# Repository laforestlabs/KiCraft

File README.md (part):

# KiCraft

KiCad PCB automation toolkit — automated placement, routing, scoring, and
experiment management for KiCad projects via the pcbnew Python API.

## Layers

KiCraft is a multi-layer pipeline. Top-down:

1. **KiCraft** (portable Agent Skills + Python helpers) -- turns a natural-
   language project description into the hierarchical KiCad 9 file set
   (root + leaf `.kicad_sch`, `.kicad_pro`, `_autoplacer.json`). The five
   LLM-authored stages live in standards-compliant skills under
   `.agents/skills/`; deterministic validation, synthesis, placement, routing,
   and fab export are Python CLIs. See [KiCraft](#kicraft-chat--kicad-files).
2. **placement + routing + scoring** (Python, this repo) -- everything below.

## Web clarification policy

The board composer places **Auto default questions?** below the brief, checked
by default. Uncheck it to answer design ambiguities yourself. The choice belongs
to the project: reopening, answering, recovery re-drives, and cloning retain it;
**New design** resets it to checked.

Interactive questions offer ordered choices with the first labeled
**Recommended default**, plus a freeform answer field. Recommendations are not
preselected: every blocking question needs an answer before continuing. Older
saved questions without recorded choices remain answerable as freeform text.
Automatic handling does not waive electrical gates or invent missing physical
requirements; unresolved internal BOM repair fails rather than asking the user
to choose a fabricated recommendation.

Stage tabs reflect streamed native/current stage events while the run is active:
amber for active or parked, green for complete, red for failure, and yellow for
warning. Icons and accessible status names distinguish states independently of
color, including on mobile.

### What the page claims: assurance and export labels

Every project carries one derived **assurance** reading, shown next to its status
and above any download. It is derived from that project's own persisted evidence
(committed stages, stage outcomes and diagnostics, review findings, the build
gate and synthesis-check summaries, and any independent verification recorded for
the run) — it is not a separate status database, so reopening a project derives
the same answer.
Completion headlines and badges describe generation, not independent product
acceptance; the assurance reading separately exposes recorded gaps and verification.

- **Software-verified complete export** — a *current*, artifact-hash-bound
  independent verification (an acceptance audit or filled acceptance evidence)
  matches this exact export. Hardware qualification is still the user's to get.
- **Generated package · independently unverified** — a clean,
  fabrication-gate-passing export with nothing recorded to review. Downloadable,
  but *not* independently verified as fulfilling the original brief. Parts
  coverage, a committed review stage, or the presence of a downloadable package
  never make an export "verified".
- **Generated with recorded gaps · review required** — the same export plus
  recorded limitations (compiler advisories, model-declared pin claims for
  unreviewed parts, unresolved requirements, review blockers, fabrication
  cautions, unapproved changes to a required part).
- **Recorded capability limitation** — an explicit reviewed-library or recipe
  resource diagnostic stopped a requirement. A compiler contract, malformed
  candidate or procurement rejection alone is an **Incomplete or failed preview**,
  not evidence that the user's requirement is unsupported. A failed search is
  not proof the circuit is impossible.
- **Incomplete or failed preview** / **Stale preview** — the build failed or
  exhausted its recovery, or the board on disk belongs to an earlier accepted
  design (an upstream edit invalidated it). The artifacts stay viewable as
  history; the page does not offer them as this design's export.
- **Waiting for your answer** — the run is parked on an unanswered blocking
  question.

Part changes are reported honestly. A substitution the BOM ledger records for a
part the **user required** is a change, not consent: unless a recorded answer
from the user approves it, the export is labelled review-required and the change
is listed as having no recorded approval. An automatic default recorded on a
cosmetic question, and a model-selected part's automatic alternative, are listed
as actions KiCraft took — never as the user's approval.

STEP exports additionally report their actual assembly-reference coverage.
Missing component bodies and unknown coverage are explicit; a model occurrence
does not qualify geometry, clearance or the rendered image. See
[`docs/ARTIFACTS.md`](docs/ARTIFACTS.md) for the package receipt and coverage contract.

### Account admission and billing safety

Design creation reserves verification, rolling tier quota and visibility in one
SQLite transaction; a separate quota pre-check does not authorize an insert.
Invite redemption and single-use account tokens are likewise atomic. Login
attempts are limited per account and trusted ASGI peer, not caller-supplied
forwarding headers.

Stripe customer and Checkout creation use durable idempotency keys and
single-owner admission. Pre-cutover open sessions/subscriptions are reconciled
before creating another chargeable session; mismatched or uncertain state is
refused. Account deletion settles open Checkout and confirms subscription
cancellation before removing local billing linkage. Unresolved requests older
than the safe idempotency window require reconciliation, not a new key.

Build jobs and project updates carry attempt generations. A prior failed worker
cannot finalize or reap a newer attempt. Cloning preserves only the selected
generation and rebases its own artifact paths; a saved design without generated
artifacts can still be cloned, without advertising an old package.

## Installation

```bash
# Development install (editable). Synthesis imports KiCad 9's bundled
# `pcbnew`; system Python already has it. For an isolated venv, create it
# with `--system-site-packages` so `pcbnew` is visible (see pipx note below).
pip install -e .

# With KiCraft design helpers (Pydantic, kicad-skip, and easyeda2kicad).
# The ordinary skill uses the active agent's configured LLM; KiCraft itself
# needs provider credentials only for the provider-backed debug/server path.
pip install -e ".[design]"

# With all optional dependencies
pip install -e ".[scoring,experiment,design,tuning,server,loadtest,dev]"
```

### End-user install (pipx)

`kicraft build` imports KiCad's bundled `pcbnew`, and
`add-part --from-lcsc` imports `easyeda2kicad`. An isolated pipx venv sees
neither by default, so install with `--system-site-packages` and the
`[design]` extra:

```bash
pipx install --system-site-packages "kicraft[design]"
```

Already installed without them? Symptoms are `add-part --from-lcsc` printing
`easyeda2kicad not installed`, or `synthesize` raising
`ModuleNotFoundError: pcbnew`. Remediate with:

```bash
pipx reinstall --system-site-packages kicraft
pipx inject kicraft easyeda2kicad   # only if the [design] extra was omitted
```

## KiCraft (chat -> KiCad files)

A multi-turn agent workflow that takes a project description in plain English
and emits the hierarchical KiCad 9 file set consumed by placement and routing.
No prior schematic is required.

### Architecture

- The five design stages (`intent`, `functional_spec`, `architecture`, `bom`,
  and `wiring`) use the `ConversationState` Pydantic schema in
  `.kicraft/state.json`.
  Completion uses the shared `stage_done` rule, not merely nonempty connections:
  a BOM can already contain compiler-owned support wiring. A successful BOM commit
  sets `wiring_complete: false`; successful wiring acceptance sets it to `true`.
  Legacy states without the marker retain status/ownership-aware recovery.
- Portable Agent Skills live under `.agents/skills/`. The ordinary `kicraft`
  skill uses whichever LLM the active agent runtime provides.
- `.omp/config.yml` points OMP at that generic directory as a custom skill
  source, so the repository skills override stale user-level copies with the
  same names.
- The optional `kicraft-debug` skill calls the production provider-backed stage
  runtime. It runs in two modes: interactive, which pauses before each durable commit for
  explicit review, and loop, which drives every stage to a committed board unattended,
  defaults anything the design can absorb (recording and analysing each default), and stops
  only on a failure it cannot repair. Both modes keep the same audit trail under
  `.kicraft/debug/`.
- The deterministic synthesis/build step is the `kicraft` CLI.

### Run it

Open this repository in any Agent Skills-compatible coding agent and ask it to
use the `kicraft` skill:

```text
Use the kicraft skill to design a USB-C powered 3.3 V status LED board.
```

For production-provider stage inspection:

```text
Use the kicraft-debug skill to walk through each KiCraft LLM stage.
```

Describe your project ("USB-C powered 3.3V regulator with status LED,
JLCPCB target, under $5 BOM"). The ordinary flow steps through all five
stages and commits each slot. The debug flow uses the production provider
and retains its prompt, raw response, tool trace, candidate, and diagnostics
under `.kicraft/debug/`. Interactive runs keep `.kicraft/state.json` unchanged
until explicit acceptance; loop runs commit each stage as soon as its own checks
pass, and write an end-of-run summary plus a machine-readable last line so a
wrapper can iterate. After wiring is committed, ask the ordinary skill to
run the deterministic build.

```bash
kicraft build .kicraft/state.json ./generated --quality good
```

### Using the skills in another project

Copy the standards-compliant skill directories into the target project's
`.agents/skills/` discovery root:

```bash
mkdir -p your-project/.agents/skills
cp -r /path/to/KiCraft/.agents/skills/kicraft your-project/.agents/skills/
cp -r /path/to/KiCraft/.agents/skills/kicraft-debug your-project/.agents/skills/
```

OMP users should also copy the small discovery bridge:

```bash
mkdir -p your-project/.omp
cp /path/to/KiCraft/.omp/config.yml your-project/.omp/
```

Clients that use a different Agent Skills discovery root can copy the same
skill directories there unchanged; each skill is self-contained around its
`SKILL.md`.

Install the ordinary design CLI with
`pip install -e "/path/to/KiCraft[design]"`. It uses the active agent's LLM
configuration and does not require a KiCraft provider key. The provider-backed
`kicraft-debug` skill additionally requires
`pip install -e "/path/to/KiCraft[server,design]"` and the OpenRouter
configuration used by the production web stage driver.

### Agent capabilities

The skills use generic capabilities rather than vendor-specific permission
syntax. Grant the active agent only the capabilities listed in each
`SKILL.md`: read project/skill files, write `/tmp/kicraft_*`, and run the named
`kicraft` commands. No slash commands, vendor-specific delegation API, or
vendor-specific settings file is required.

### CLI reference

```bash
kicraft stage-prep <stage> [STATE]
# Single-shot collector. Returns JSON: {state, extras} where extras carries
# the leaf-library output for architecture and BATCHED symbol pinouts for
# wiring (replacing N per-part lookup-symbol calls with one).

kicraft stage-commit <stage> --slot-file F.json \
  [--questions-file Q.json] [--history-message M] [--project-stem S] \
  [--invalidate-downstream] [STATE] [--no-archive] [--archive-root DIR]
# Atomic: validate the proposed slot, merge into state.json, append history,
# archive. Returns {"ok": true, ...} or {"ok": false, "errors": [...]} so the
# active agent can correct a rejected candidate.

kicraft-stage-debug debug-draft --workspace PATH --stage STAGE \
  --brief-file BRIEF [--instruction-file GUIDANCE] [--answers-file ANSWERS]
# Runs the production provider and atomically saves a pending review artifact
# without committing or stamping state.json.

kicraft-stage-debug debug-commit --workspace PATH --stage STAGE \
  --history-message-file MESSAGE
# Stale-hash checks state.json, commits the exact accepted slot through
# stage-commit, invalidates downstream stages, and finalizes the debug trace.

kicraft validate .kicraft/state.json
# prints {ok, project_stem, slots_filled, open_questions, blocking_questions}
# exit codes: 0 ok, 2 schema error, 3 library validation error

kicraft list-leaves
# prints the "Available leaves" markdown block. The architecture stage
# receives this via stage-prep's extras; this command is for ad-hoc inspection.

kicraft lookup-symbol Library:Name
# prints one symbol's pin inventory. The wiring stage receives all needed
# pinouts via stage-prep's batched extras; this command is for ad-hoc lookup.

kicraft synthesize .kicraft/state.json ./generated [--smoke]
# wraps kicraft.design.synthesize.run; --smoke adds the (slow)
# solve-subcircuits check
```

### What gets written

For project stem `MYPROJ`, synthesis writes:

```
MYPROJ/
  MYPROJ.kicad_sch                    # hierarchical root
  <SHEET>.kicad_sch ...               # one per leaf sheet
  MYPROJ.kicad_pro                    # design rules + Default/Power netclasses
  MYPROJ_autoplacer.json              # ic_groups, power_nets, signal_flow_order, ...
  MYPROJ.kicad_pcb                    # empty pcbnew stub
```

Managed web builds isolate each attempt under
`generated/attempt-<generation>/<STEM>/`; requeued work retains that attempt's
directory. `state.artifacts.project_dir` identifies the recorded output, but
previews and downloads must also belong to the current attempt. Older outputs
remain evidence, not current delivery.

Synthesis records hashes of the generated files it owns. An explicit CLI output
directory containing untracked or user-modified outputs is refused rather than
silently adopted or overwritten. Completed partial outputs are recorded so a
failed attempt can recover without claiming unrelated files.

Everything past that is the existing layout/routing pipeline:

```bash
cd MYPROJ
autoexperiment MYPROJ.kicad_pcb --schematic MYPROJ.kicad_sch --rounds 20
```

### Validation

Every synthesis run executes SS9.1-SS9.6 from
`docs/kicraft_schematic_prompt.md` against the written files
(schematic version, footprints non-empty, pin directions valid,
Sheetfile refs resolve, autoplacer JSON valid, every named ref in
the schematic). Synthesis raises `SynthesisValidationError` and prints
the failing check rather than shipping a broken file set.

### Notes

- Resolved curated bundles can provide project-local symbols, footprints and
  models. An unresolved or unqualified part remains blocking; a matching name
  or stock count alone does not establish electrical or physical suitability.
- State persists as `.kicraft/state.json` in the project directory —
  gitignore it (or commit it; it's plain JSON and reviewable).

## Leaf Library (reuse vetted designs across projects)

A *leaf* is a single hierarchical sheet — a pre-routed PCB fragment plus
its schematic, BOM, and autoplacer settings. Once you've solved one
("USB-C 1S LiPo charger") and pinned a round you trust, you can promote
it into the global Leaf Library. The KiCraft pipeline then reuses
it verbatim every time the LLM judges it a match for a new project,
collapsing leaf-level design surface to a vetted, pinned solution.

### Where leaves live

```
$KICRAFT_LEAF_LIB                # default: ~/.kicraft/leaves/
  usb-c-lipo-charger/
    manifest.json
    leaf_routed.kicad_pcb        # canonical name (matches .experiments/...)
    metadata.json
    solved_layout.json
    schematic.kicad_sch
    autoplacer_fragment.json
    bom.csv
    renders/
      front_all.png
      back_copper.png
      copper_both.png
      thumbnail.png
```

The pinned-PCB triad (`leaf_routed.kicad_pcb` + `metadata.json` +
`solved_layout.json`) is the same triad the existing pin manager (under
`.experiments/subcircuits/<leaf_key>/`) consumes, so an imported leaf
drops in as a pre-solved round and the parent composer treats it as
already-solved on the next `autoexperiment --parents-only`.

### Promote a leaf

> **Note:** the Experiment Manager GUI that hosted the "Leaf Library" promote flow was
> removed 2026-06-22 (recover from git history if needed). Leaf promotion is pending a
> re-home in the web app — see `docs/plans/refactor-roadmap.md`. The pinned-round import
> format described above still applies.

The wizard runs the renders, writes a manifest with the
content-addressed hash, and atomically writes the new directory into
`$KICRAFT_LEAF_LIB`. To replace an existing leaf, bump the version
(e.g. `0.1.0 -> 0.1.1` for a patch, `0.2.0` for additive interface
changes, `1.0.0` for breaking ones).

### Automatic reuse during KiCraft

When the skill enters the architecture stage it runs
`kicraft list-leaves` and reads the result so the model can
see the curated catalog. The active agent picks matches by setting
`Sheet.from_library = "<name>@<version>"` and `Sheet.library_instance = N`.
`kicraft validate` then verifies the leaf's hierarchical-
label interface matches the sheet's endpoints exactly. Synthesis then:

1. Skips the LLM-generated leaf schematic for that sheet.
2. Copies the leaf's `schematic.kicad_sch` to the project (with refdes
   renumbered to fit the host project's existing refs).
3. Writes the renumbered triad into
   `<project>/.experiments/subcircuits/<leaf_key>/round_lib0001_*`.
4. Pins the import via `pins.json` so `ensure_applied()` keeps it locked
   across solver runs.
5. Adds a `library_leaves` audit record to `<project>_autoplacer.json`.

### CLI

```bash
kicraft-leaf list             # rows: name@version, hash, tags, description
kicraft-leaf show <name>      # full manifest as JSON
kicraft-leaf path             # resolved library directory
```

Promotion and removal are GUI-only — there's no `kicraft-leaf promote`.
The intent is that curating the library is a deliberate, human-in-loop
step, not a scriptable one.

## Quick Start

KiCraft is project-agnostic. Create a `<project>_autoplacer.json` (or
`autoplacer.json`) in your KiCad project root to configure IC groups,
component zones, signal flow, and other project-specific settings.

See `examples/llups_autoplacer.json` for a full example.

### Solve subcircuits

```bash
cd /path/to/your/kicad-project
solve-subcircuits project.kicad_sch --pcb project.kicad_pcb --rounds 3 --route
```

### Run experiment loop

```bash
autoexperiment project.kicad_pcb project.kicad_sch --rounds 20 --workers 2
```

### Two-phase guided experiment (leaf pinning)

Explore leaf candidates first, lock the ones you like, then iterate on the
parent only:

```bash
# 1. Solve only leaves -- snapshots every round to .experiments/subcircuits/<leaf>/round_NNNN_*
autoexperiment project.kicad_pcb --schematic project.kicad_sch --rounds 30 --leaves-only

# 2. Pin chosen rounds via the GUI Analysis page (Hierarchical Progression -> Accepted
#    Leaf Gallery -> "Pin from prior experiment-round snapshots"), or write
#    .experiments/pins.json by hand.

# 3. Run only the parent compose phase against the pinned leaves
autoexperiment project.kicad_pcb --schematic project.kicad_sch --rounds 10 --parents-only
```

The composer calls `pins.ensure_applied()` before loading artifacts, so
pinned leaves stay locked even if a stray leaf-solve overwrites the
canonical files. The best parent of any run is also copied to
`.experiments/best/parent_routed.kicad_pcb` and `<projectname>_best.kicad_pcb`
at the project root for fab handoff.

### Score a layout

```bash
score-layout project.kicad_pcb
```

### Configuring Placement

Placement constraints live in `<project>_autoplacer.json` at the project
root. The autoplacer auto-discovers it; the file is project-agnostic --
it references components by ref designator (e.g. `J1`) or subcircuit
sheet name (e.g. `BATT`), nothing is hardcoded to a particular project.
See `examples/llups_autoplacer.json` for a full working file.

#### Pinning components to edges, corners, or zones

`component_zones` constrains where individual refs land on the board.
Three constraint types, all applied at solve time:

```json
{
  "component_zones": {
    "J1":  { "edge":   "left" },
    "J2":  { "edge":   "right" },
    "H4":  { "corner": "top-left" },
    "H86": { "corner": "bottom-right" },
    "BT1": { "zone":   "bottom" },
    "BT2": { "zone":   "bottom" }
  }
}
```

* `edge: left|right|top|bottom` — connector body flush with the named
  edge. Pads face inward, housing overhangs outward by
  `connector_edge_inset_mm`.
* `corner: top-left|top-right|bottom-left|bottom-right` — typically
  mounting holes. Locks at the corner with `mounting_holes.keepout.size_mm`
  reserved (see [Mounting holes](#mounting-holes) below).
* `zone: top|bottom|left|right|...` — soft confinement to a region.
  The component is locked inside the zone; the solver may place it
  anywhere within it.

When a ref is part of a child subcircuit (e.g. `BT1` inside the `BATT`
subcircuit), the constraint is propagated to the *block* during parent
composition, so the BATT block ends up zone-bottom-pinned at parent
solve time.

#### Backside THT components: enabling stacking

By default, the parent composer prevents two leaves from overlapping
when both have any same-layer copper -- a strict same-layer-outline
gate that catches CHARGER-style continuous-F.Cu shorts. PTH pads
register as copper on **both** F.Cu and B.Cu, so a leaf whose only
front-side copper is the shadow of through-hole pads (battery
holders, screw terminals, large barrel jacks) is treated as having
real F.Cu occupancy and rejects SMT-on-front stacking inside its
bbox -- even when the body centre is empty and stacking would be
physically fine.

To re-enable opposite-side stacking on top of such a leaf, open the
GUI's **Setup → Per-Component Placement Rules** tab, expand the leaf,
and toggle the sheet-level switch:

> ☐ → ☑ **Backside THT anchor (allow SMT-front leaves to stack on top)**

Click **Save to project JSON…**, review the diff modal, and confirm.
The toggle persists as a sheet-name entry under
`parent_placement.backside_through_hole_leaves`. For headless or CI
workflows the same key can be set by hand:

```json
{
  "parent_placement": {
    "backside_through_hole_leaves": ["BATT", "TERMINAL_BLOCK"]
  }
}
```

What the override does:

* Marks the leaf as having no F.Cu intent for the same-layer-outline
  gate, so SMT-on-front leaves may overlap inside its bbox.
* Tells the post-SA stack pass (`_stack_compatible_blocks`) to use
  it as a stacking anchor, actively row-packing front-only candidates
  inside its body.
* Leaves the per-pad sparse-rect overlap checks in place -- if a
  candidate's pads happen to land on the THT pads themselves
  (corner positions), the predicate still rejects that specific
  geometry.

The flag is keyed by `sheet_name` so any project can list its own
THT-back leaves; nothing is hardcoded to a single board. CHARGER-style
leaves with continuous F.Cu routing **must not** be enabled -- the
override there would let the original same-layer shorts return.

#### Candidate search

`parent_placement.candidate_search` controls the K-candidate search
loop. The picker stamps each candidate, runs DRC, scores by a
composite of opposite-side packing, courtyard overlap, ratsnest
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
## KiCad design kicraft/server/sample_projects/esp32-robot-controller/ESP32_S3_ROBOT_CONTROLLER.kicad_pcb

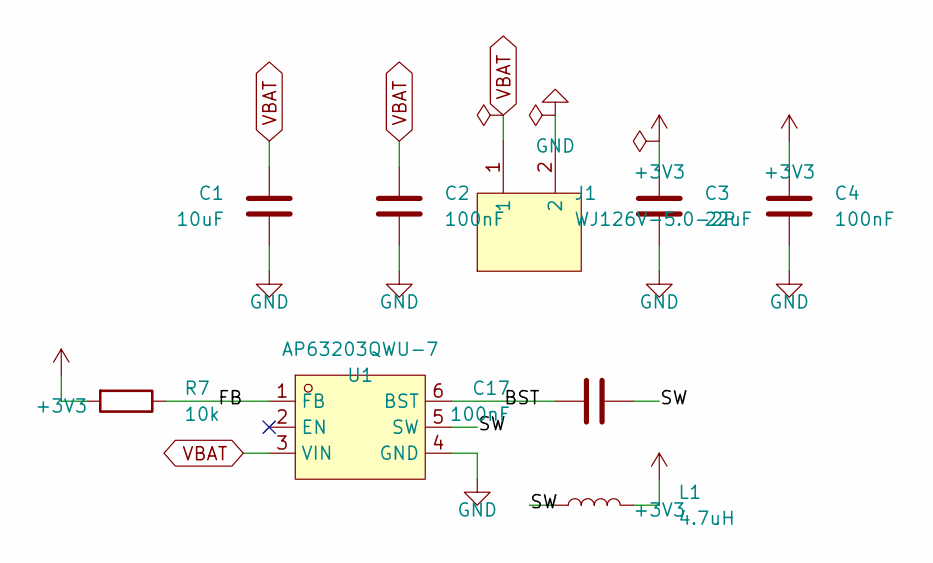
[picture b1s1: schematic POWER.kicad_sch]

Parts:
C1: 10uF; C_0805_2012Metric
C2, C4, C17: 100nF; C_0603_1608Metric
C3: 22uF; C_0805_2012Metric
J1: WJ126V-5.0-2P; CONN-TH_WJ126V-5.0-2P
L1: 4.7uH; L_0805_2012Metric
R7: 10k; R_0603_1608Metric
U1: AP63203QWU-7; TSOT-26_L2.9-W1.6-P0.95-LS2.8-BL

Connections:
BST: C17.1, U1.6 (BST)
FB: R7.1, U1.1 (FB)
SW: C17.2, L1.1, U1.5 (SW)

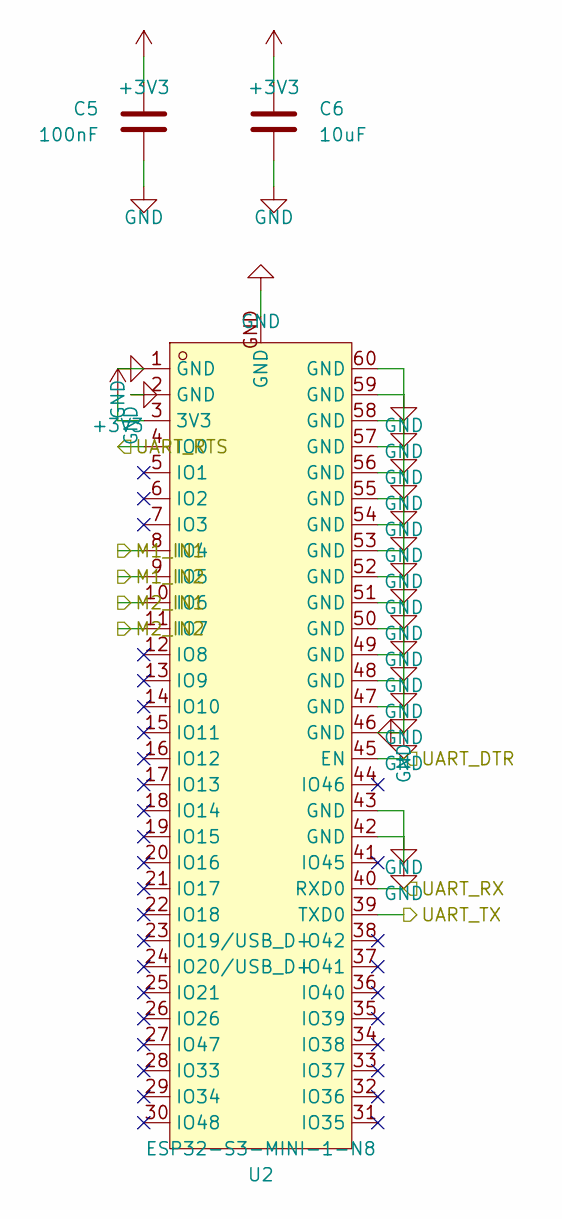
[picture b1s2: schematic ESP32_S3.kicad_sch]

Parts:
C5: 100nF; C_0603_1608Metric
C6: 10uF; C_0805_2012Metric
U2: ESP32-S3-MINI-1-N8; BULETM-SMD_ESP32-S3-MINI-1-N8

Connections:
M1_IN1: U2.8 (IO4); also elsewhere on the board
M1_IN2: U2.9 (IO5); also elsewhere on the board
M2_IN1: U2.10 (IO6); also elsewhere on the board
M2_IN2: U2.11 (IO7); also elsewhere on the board
UART_DTR: U2.45 (EN); also elsewhere on the board
UART_RTS: U2.4 (IO0); also elsewhere on the board
UART_RX: U2.40 (RXD0); also elsewhere on the board
UART_TX: U2.39 (TXD0); also elsewhere on the board

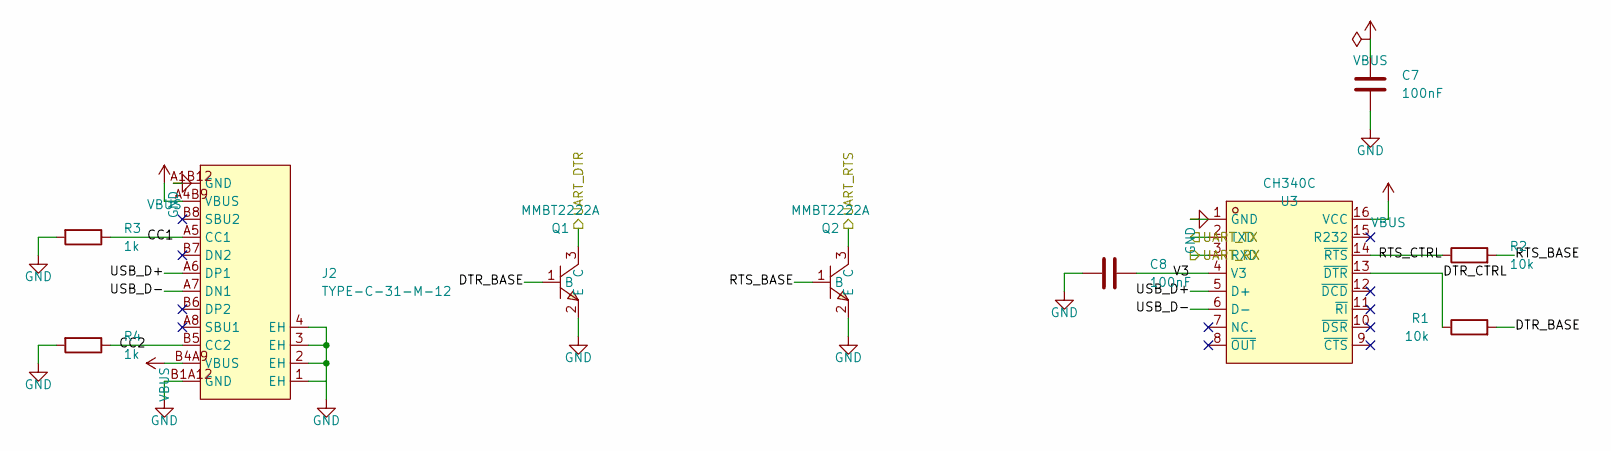
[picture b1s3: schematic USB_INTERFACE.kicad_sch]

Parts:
C7, C8: 100nF; C_0603_1608Metric
J2: TYPE-C-31-M-12; USB-C_SMD-TYPE-C-31-M-12_1
Q1, Q2: MMBT2222A; SOT-23-3_L2.9-W1.3-P1.90-LS2.4-BR
R1, R2: 10k; R_0603_1608Metric
R3, R4: 1k; R_0603_1608Metric
U3: CH340C; SOP-16_L10.0-W3.9-P1.27-LS6.0-BL

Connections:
CC1: J2.A5 (CC1), R3.1
CC2: J2.B5 (CC2), R4.1
DTR_BASE: Q1.1 (B), R1.2
DTR_CTRL: R1.1, U3.13 (~DTR)
RTS_BASE: Q2.1 (B), R2.2
RTS_CTRL: R2.1, U3.14 (~RTS)
UART_DTR: Q1.3 (C); also elsewhere on the board
UART_RTS: Q2.3 (C); also elsewhere on the board
UART_RX: U3.3 (RXD); also elsewhere on the board
UART_TX: U3.2 (TXD); also elsewhere on the board
USB_D+: J2.A6 (DP1), U3.5 (D+)
USB_D-: J2.A7 (DN1), U3.6 (D-)
V3: C8.1, U3.4 (V3)
VBUS: C7.1, J2.A4B9 (VBUS), J2.B4A9 (VBUS), U3.16 (VCC)

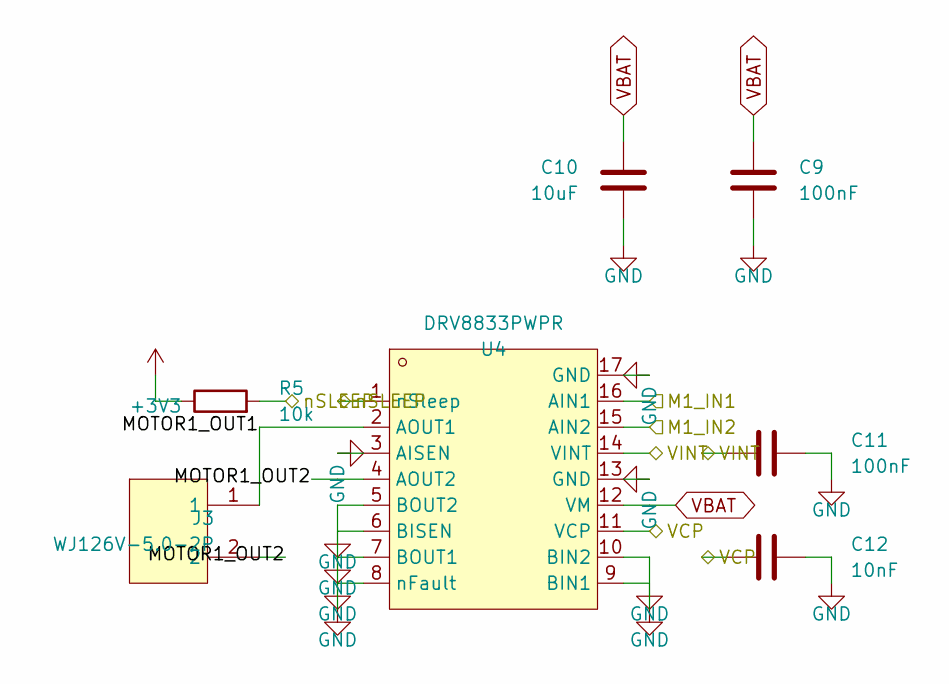
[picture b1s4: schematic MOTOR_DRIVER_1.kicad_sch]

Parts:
C9, C11: 100nF; C_0603_1608Metric
C10: 10uF; C_0805_2012Metric
C12: 10nF; C_0603_1608Metric
J3: WJ126V-5.0-2P; CONN-TH_WJ126V-5.0-2P
R5: 10k; R_0603_1608Metric
U4: DRV8833PWPR; TSSOP-16_L5.0-W4.4-P0.65-LS6.4-BL-EP

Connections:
M1_IN1: U4.16 (AIN1); also elsewhere on the board
M1_IN2: U4.15 (AIN2); also elsewhere on the board
MOTOR1_OUT1: J3.1, U4.2 (AOUT1)
MOTOR1_OUT2: J3.2, U4.4 (AOUT2)
VCP: C12.1, U4.11 (VCP); also elsewhere on the board
VINT: C11.1, U4.14 (VINT); also elsewhere on the board
nSLEEP: R5.2, U4.1 (nSleep); also elsewhere on the board

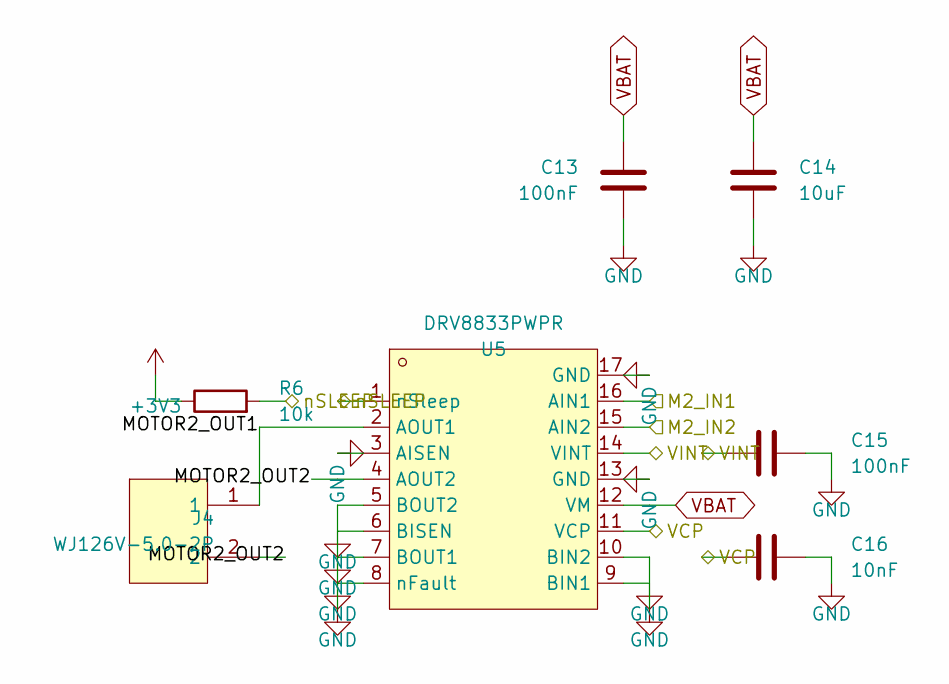
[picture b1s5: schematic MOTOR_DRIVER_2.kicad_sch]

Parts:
C13, C15: 100nF; C_0603_1608Metric
C14: 10uF; C_0805_2012Metric
C16: 10nF; C_0603_1608Metric
J4: WJ126V-5.0-2P; CONN-TH_WJ126V-5.0-2P
R6: 10k; R_0603_1608Metric
U5: DRV8833PWPR; TSSOP-16_L5.0-W4.4-P0.65-LS6.4-BL-EP

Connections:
M2_IN1: U5.16 (AIN1); also elsewhere on the board
M2_IN2: U5.15 (AIN2); also elsewhere on the board
MOTOR2_OUT1: J4.1, U5.2 (AOUT1)
MOTOR2_OUT2: J4.2, U5.4 (AOUT2)
VCP: C16.1, U5.11 (VCP); also elsewhere on the board
VINT: C15.1, U5.14 (VINT); also elsewhere on the board
nSLEEP: R6.2, U5.1 (nSleep); also elsewhere on the board

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
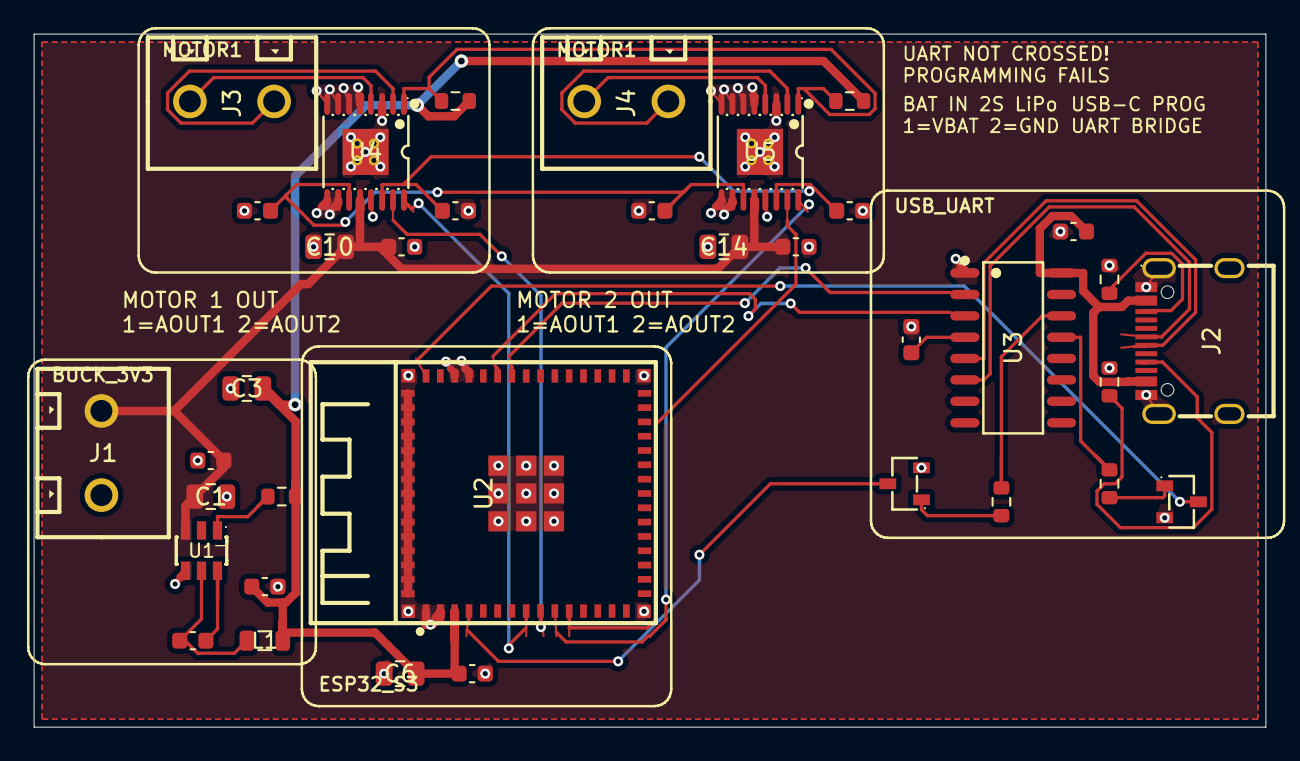
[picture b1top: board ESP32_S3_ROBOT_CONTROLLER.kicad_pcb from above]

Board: 2 copper layers, 73.2 x 41.2 mm, 36 parts (0 on the bottom side), 31 nets.

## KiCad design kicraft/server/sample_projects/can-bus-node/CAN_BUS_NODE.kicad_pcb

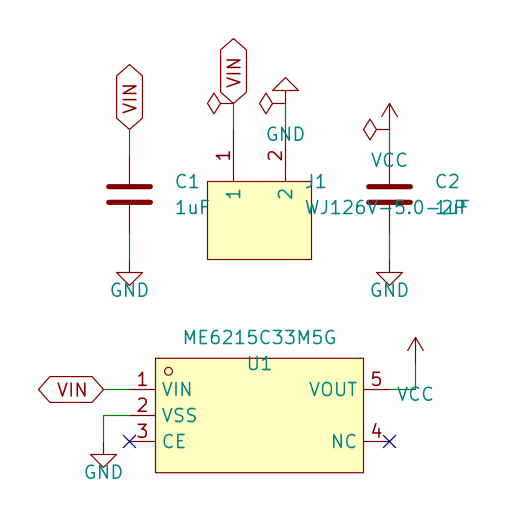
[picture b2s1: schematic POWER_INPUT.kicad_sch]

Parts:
C1, C2: 1uF; C_0603_1608Metric
J1: WJ126V-5.0-2P; CONN-TH_WJ126V-5.0-2P
U1: ME6215C33M5G; SOT-23-5_L3.0-W1.7-P0.95-LS2.8-BR

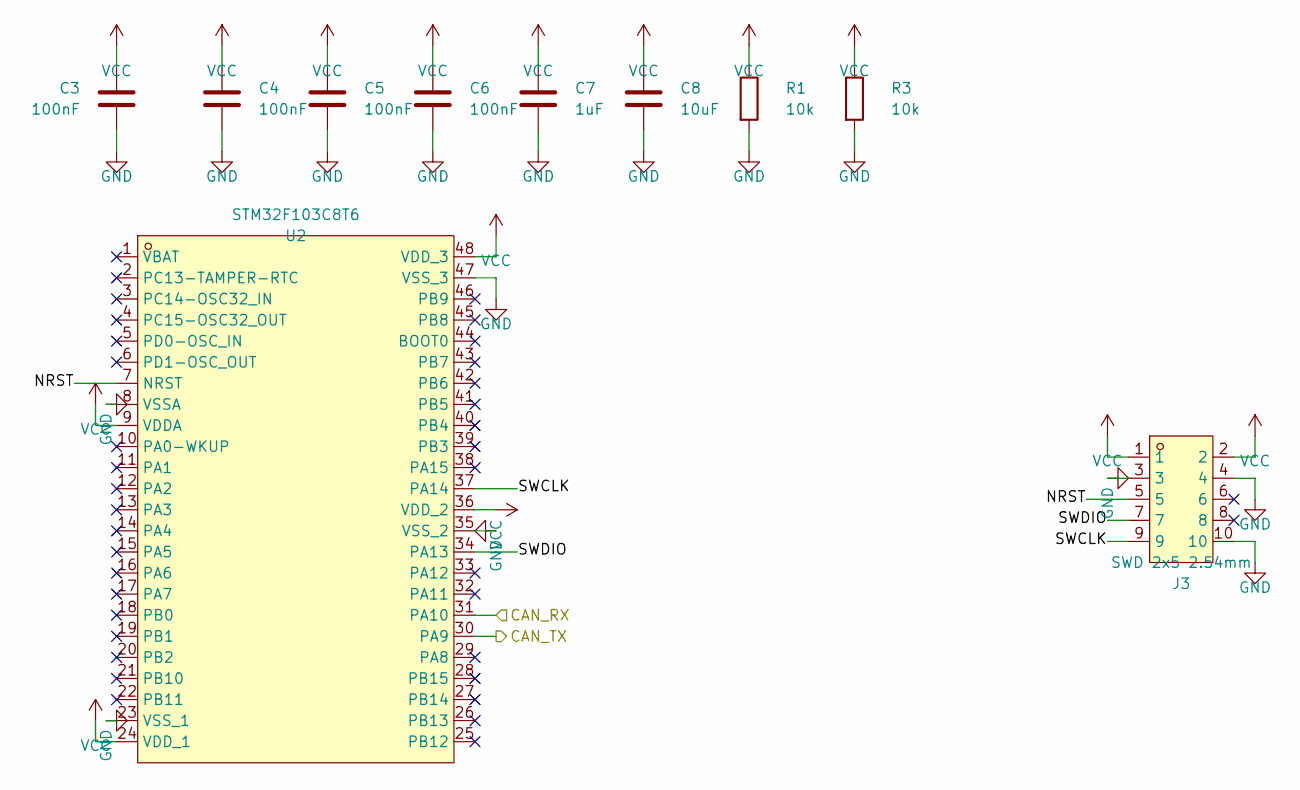
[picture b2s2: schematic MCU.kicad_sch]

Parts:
C3, C4, C5, C6: 100nF; C_0603_1608Metric
C7: 1uF; C_0603_1608Metric
C8: 10uF; C_0603_1608Metric
J3: SWD 2x5 2.54mm; HDR-TH_10P-P2.54-V-M-R2-C5-S2.54
R1, R3: 10k; R_0603_1608Metric
U2: STM32F103C8T6; LQFP-48_L7.0-W7.0-P0.50-LS9.0-BL

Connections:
CAN_RX: U2.31 (PA10); also elsewhere on the board
CAN_TX: U2.30 (PA9); also elsewhere on the board
NRST: J3.5, U2.7 (NRST)
SWCLK: J3.9, U2.37 (PA14)
SWDIO: J3.7, U2.34 (PA13)

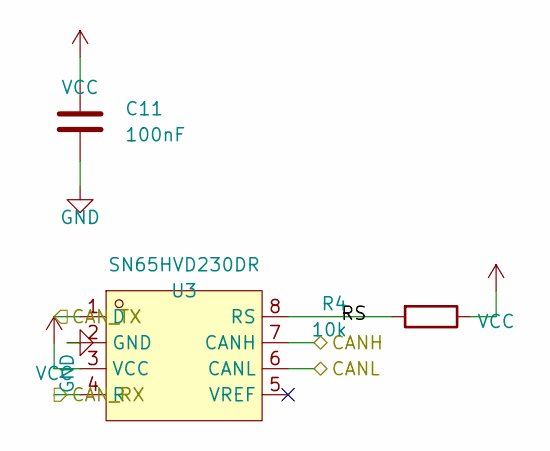
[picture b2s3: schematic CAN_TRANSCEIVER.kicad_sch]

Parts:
C11: 100nF; C_0603_1608Metric
R4: 10k; R_0603_1608Metric
U3: SN65HVD230DR; SOIC-8_L4.9-W3.9-P1.27-LS6.0-BL

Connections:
CANH: U3.7 (CANH); also elsewhere on the board
CANL: U3.6 (CANL); also elsewhere on the board
CAN_RX: U3.4 (R); also elsewhere on the board
CAN_TX: U3.1 (D); also elsewhere on the board
RS: R4.2, U3.8 (RS)

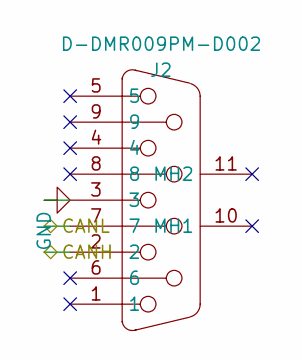
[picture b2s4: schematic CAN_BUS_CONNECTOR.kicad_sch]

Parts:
J2: D-DMR009PM-D002; DSUB-TH_DMR-9P

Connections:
CANH: J2.2; also elsewhere on the board
CANL: J2.7; also elsewhere on the board

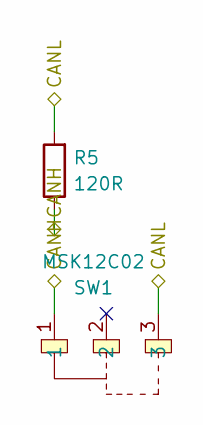
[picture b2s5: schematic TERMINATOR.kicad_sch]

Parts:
R5: 120R; R_0603_1608Metric
SW1: MSK12C02; SW-SMD_3P-L9.1-W3.5-P2.50_MST-12D18G2

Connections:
CANH: R5.1, SW1.1; also elsewhere on the board
CANL: R5.2, SW1.3; also elsewhere on the board

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
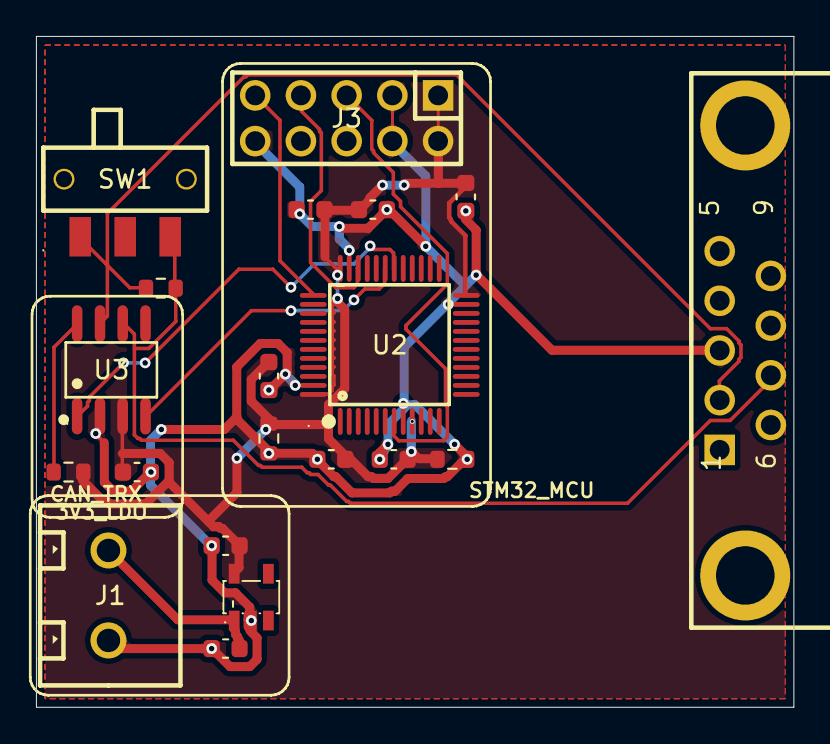
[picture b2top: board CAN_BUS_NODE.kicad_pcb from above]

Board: 2 copper layers, 42.1 x 37.3 mm, 20 parts (0 on the bottom side), 11 nets.

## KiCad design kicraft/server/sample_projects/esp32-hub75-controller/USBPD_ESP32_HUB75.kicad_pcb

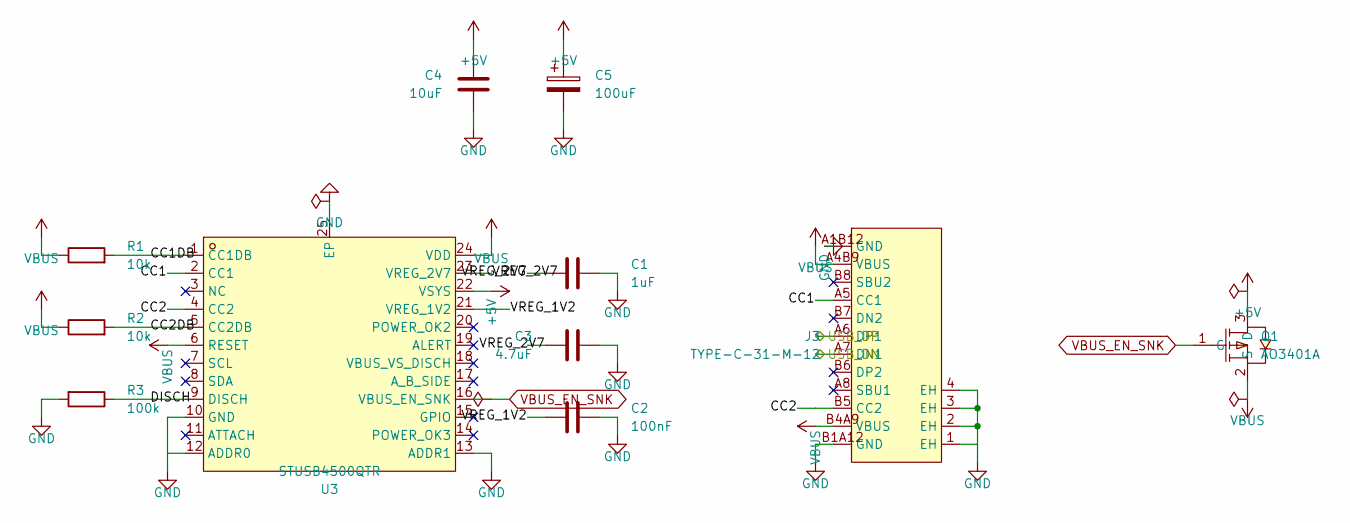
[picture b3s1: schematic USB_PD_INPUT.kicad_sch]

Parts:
C1: 1uF; C_0603_1608Metric
C2: 100nF; C_0603_1608Metric
C3: 4.7uF; C_0603_1608Metric
C4: 10uF; C_0603_1608Metric
C5: 100uF; CP_Elec_6.3x5.4
J3: TYPE-C-31-M-12; USB-C_SMD-TYPE-C-31-M-12_1
Q1: AO3401A; SOT-23_L2.9-W1.3-P1.90-LS2.4-BR
R1, R2: 10k; R_0603_1608Metric
R3: 100k; R_0603_1608Metric
U3: STUSB4500QTR; QFN-24_L4.0-W4.0-P0.50-BL-EP2.8

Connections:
CC1: J3.A5 (CC1), U3.2 (CC1)
CC1DB: R1.2, U3.1 (CC1DB)
CC2: J3.B5 (CC2), U3.4 (CC2)
CC2DB: R2.2, U3.5 (CC2DB)
DISCH: R3.1, U3.9 (DISCH)
USB_DN: J3.A7 (DN1); also elsewhere on the board
USB_DP: J3.A6 (DP1); also elsewhere on the board
VREG_1V2: C2.1, U3.21 (VREG_1V2)
VREG_2V7: C1.1, C3.1, U3.23 (VREG_2V7)

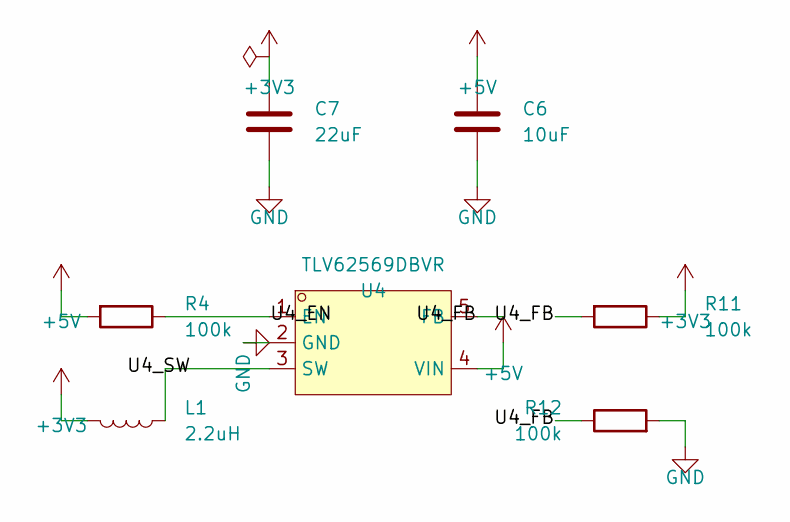
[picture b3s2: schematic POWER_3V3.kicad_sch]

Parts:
C6: 10uF; C_0603_1608Metric
C7: 22uF; C_0603_1608Metric
L1: 2.2uH; L_0805_2012Metric
R4, R11, R12: 100k; R_0603_1608Metric
U4: TLV62569DBVR; SOT-23-5_L3.0-W1.7-P0.95-LS2.8-BR

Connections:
+3V3: C7.1, L1.2, R11.1; also elsewhere on the board
U4_EN: R4.1, U4.1 (EN)
U4_FB: R11.2, R12.1, U4.5 (FB)
U4_SW: L1.1, U4.3 (SW)

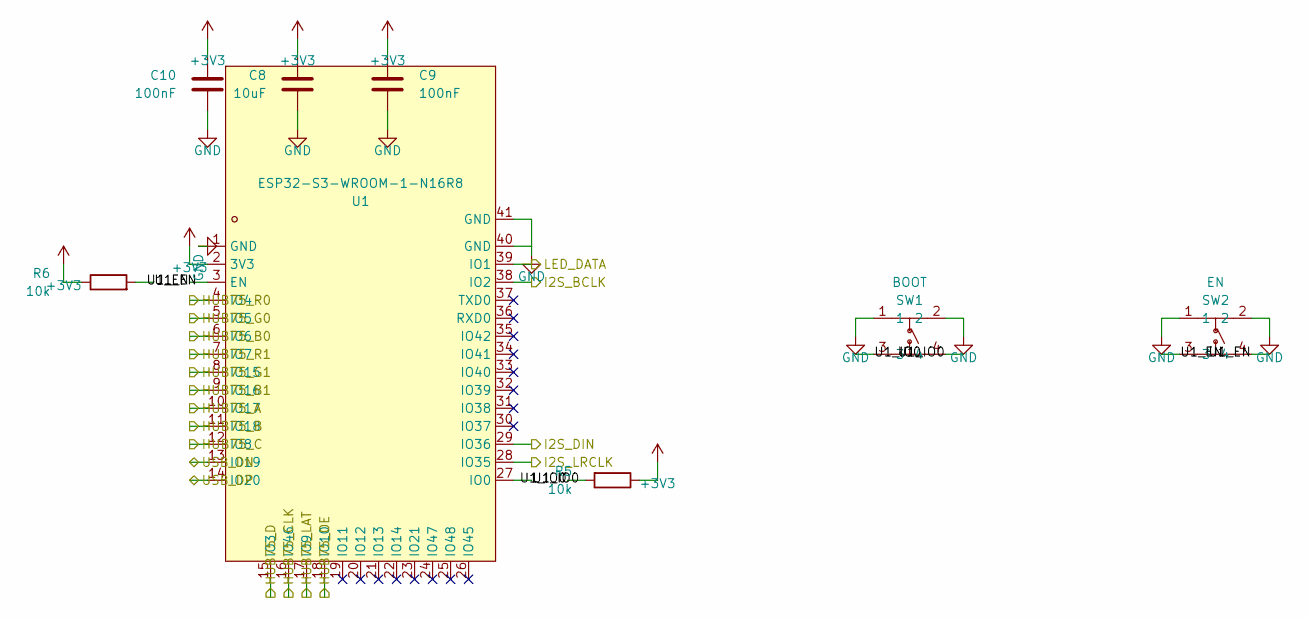
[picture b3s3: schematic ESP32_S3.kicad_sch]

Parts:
C8: 10uF; C_0603_1608Metric
C9, C10: 100nF; C_0603_1608Metric
R5, R6: 10k; R_0603_1608Metric
SW1: BOOT; SW-SMD_4P-L6.0-W6.0-P4.50-LS9.0_H5.0
SW2: EN; SW-SMD_4P-L6.0-W6.0-P4.50-LS9.0_H5.0
U1: ESP32-S3-WROOM-1-N16R8; WIRELM-SMD_ESP32-S3-WROOM-1

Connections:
+3V3: C8.1, C9.1, C10.1, R5.1, R6.1, U1.2 (3V3); also elsewhere on the board
HUB75_A: U1.10 (IO17); also elsewhere on the board
HUB75_B: U1.11 (IO18); also elsewhere on the board
HUB75_B0: U1.6 (IO6); also elsewhere on the board
HUB75_B1: U1.9 (IO16); also elsewhere on the board
HUB75_C: U1.12 (IO8); also elsewhere on the board
HUB75_CLK: U1.16 (IO46); also elsewhere on the board
HUB75_D: U1.15 (IO3); also elsewhere on the board
HUB75_G0: U1.5 (IO5); also elsewhere on the board
HUB75_G1: U1.8 (IO15); also elsewhere on the board
HUB75_LAT: U1.17 (IO9); also elsewhere on the board
HUB75_OE: U1.18 (IO10); also elsewhere on the board
HUB75_R0: U1.4 (IO4); also elsewhere on the board
HUB75_R1: U1.7 (IO7); also elsewhere on the board
I2S_BCLK: U1.38 (IO2); also elsewhere on the board
I2S_DIN: U1.29 (IO36); also elsewhere on the board
I2S_LRCLK: U1.28 (IO35); also elsewhere on the board
LED_DATA: U1.39 (IO1); also elsewhere on the board
U1_EN: R6.2, SW2.3, SW2.4, U1.3 (EN)
U1_IO0: R5.2, SW1.3, SW1.4, U1.27 (IO0)
USB_DN: U1.13 (IO19); also elsewhere on the board
USB_DP: U1.14 (IO20); also elsewhere on the board

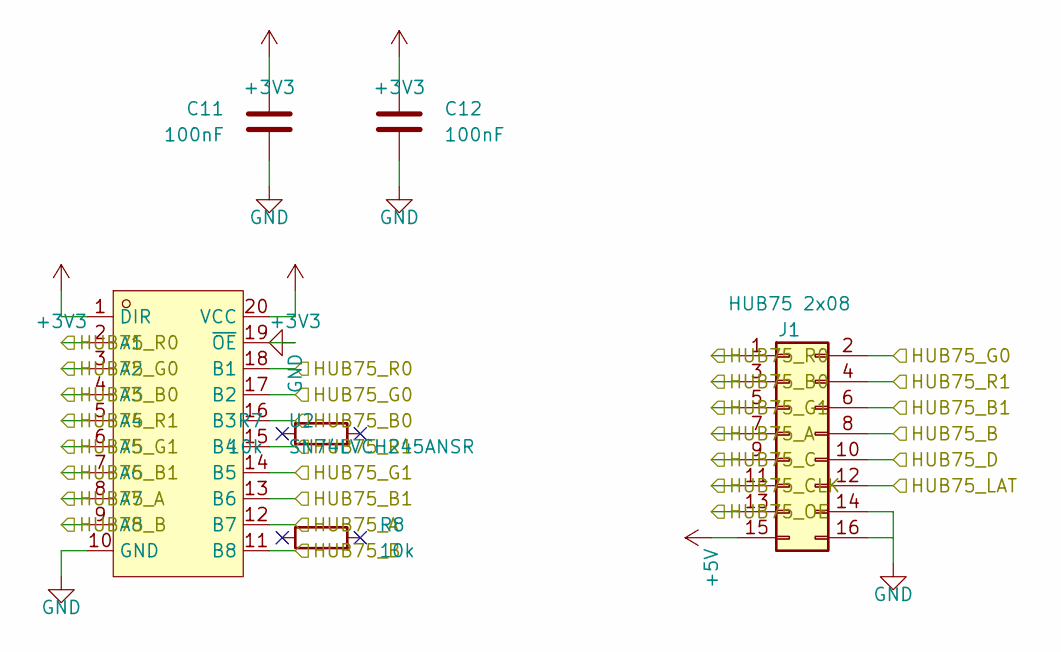
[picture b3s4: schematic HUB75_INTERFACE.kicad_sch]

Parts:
C11, C12: 100nF; C_0603_1608Metric
J1: HUB75 2x08; PinHeader_2x08_P2.54mm_Vertical
R7, R8: 10k; R_0603_1608Metric
U2: SN74LVCH245ANSR; SO-20_L12.6-W5.3-P1.27-LS7.8-BL

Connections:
+3V3: C11.1, C12.1, U2.1 (DIR), U2.20 (VCC); also elsewhere on the board
HUB75_A: J1.7, U2.8 (A7), U2.12 (B7); also elsewhere on the board
HUB75_B: J1.8, U2.9 (A8), U2.11 (B8); also elsewhere on the board
HUB75_B0: J1.3, U2.4 (A3), U2.16 (B3); also elsewhere on the board
HUB75_B1: J1.6, U2.7 (A6), U2.13 (B6); also elsewhere on the board
HUB75_C: J1.9; also elsewhere on the board
HUB75_CLK: J1.11; also elsewhere on the board
HUB75_D: J1.10; also elsewhere on the board
HUB75_G0: J1.2, U2.3 (A2), U2.17 (B2); also elsewhere on the board
HUB75_G1: J1.5, U2.6 (A5), U2.14 (B5); also elsewhere on the board
HUB75_LAT: J1.12; also elsewhere on the board
HUB75_OE: J1.13; also elsewhere on the board
HUB75_R0: J1.1, U2.2 (A1), U2.18 (B1); also elsewhere on the board
HUB75_R1: J1.4, U2.5 (A4), U2.15 (B4); also elsewhere on the board

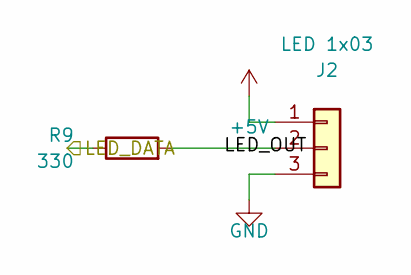
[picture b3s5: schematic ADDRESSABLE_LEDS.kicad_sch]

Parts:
J2: LED 1x03; PinHeader_1x03_P2.54mm_Vertical
R9: 330; R_0603_1608Metric

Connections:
LED_DATA: R9.1; also elsewhere on the board
LED_OUT: J2.2, R9.2

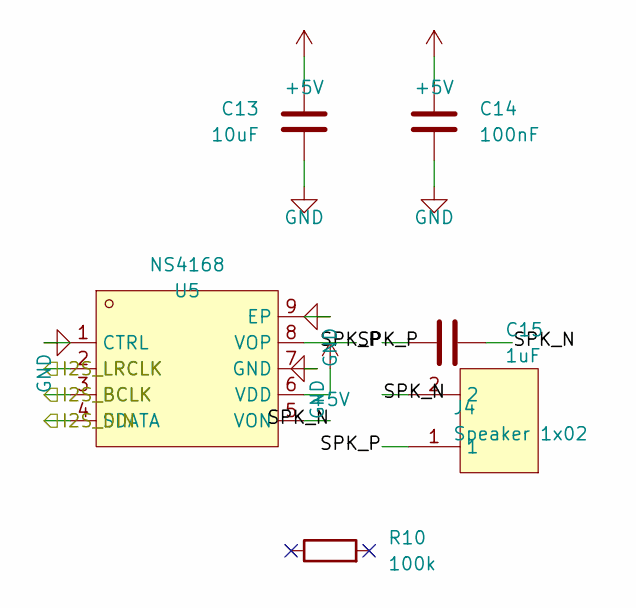
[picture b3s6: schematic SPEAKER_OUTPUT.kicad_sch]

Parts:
C13: 10uF; C_0603_1608Metric
C14: 100nF; C_0603_1608Metric
C15: 1uF; C_0603_1608Metric
J4: Speaker 1x02; CONN-TH_WJ126V-5.0-2P
R10: 100k; R_0603_1608Metric
U5: NS4168; ESOP-8_L4.9-W3.9-P1.27-LS6.0-BL-EP

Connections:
I2S_BCLK: U5.3 (BCLK); also elsewhere on the board
I2S_DIN: U5.4 (SDATA); also elsewhere on the board
I2S_LRCLK: U5.2 (LRCLK); also elsewhere on the board
SPK_N: C15.2, J4.2, U5.5 (VON)
SPK_P: C15.1, J4.1, U5.8 (VOP)

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
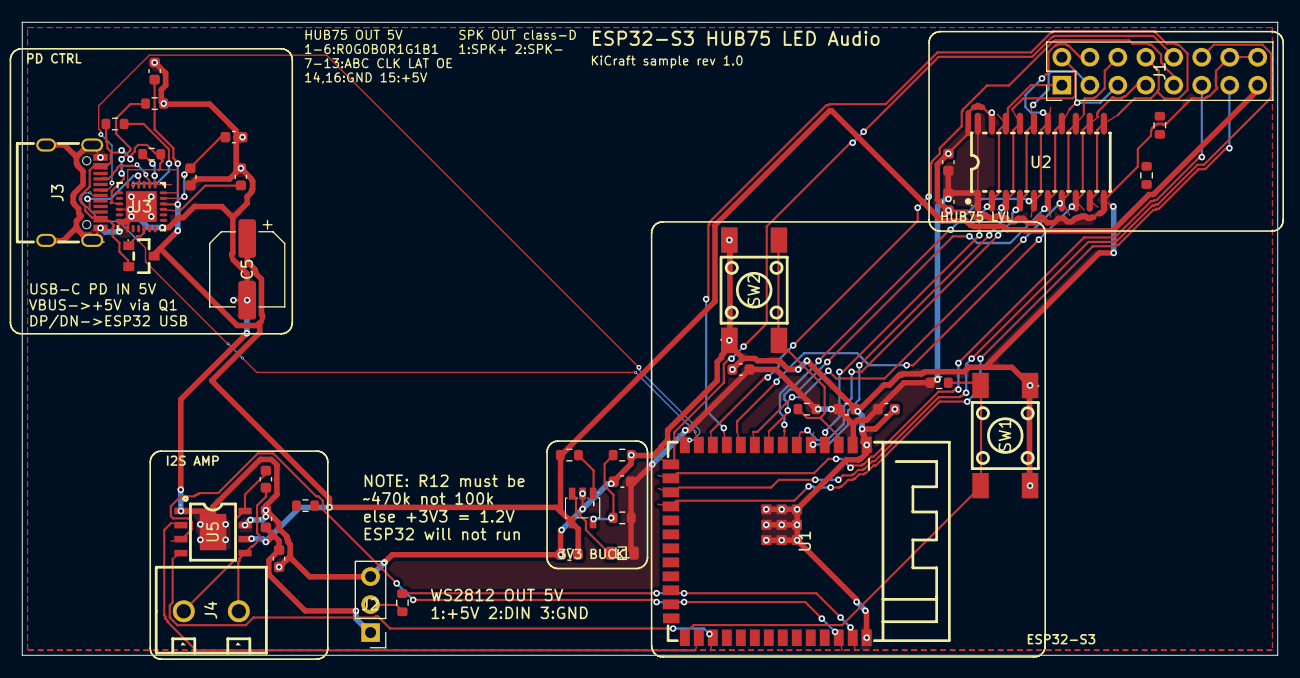
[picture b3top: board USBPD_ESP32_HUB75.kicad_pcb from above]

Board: 2 copper layers, 114.0 x 57.5 mm, 40 parts (0 on the bottom side), 39 nets.

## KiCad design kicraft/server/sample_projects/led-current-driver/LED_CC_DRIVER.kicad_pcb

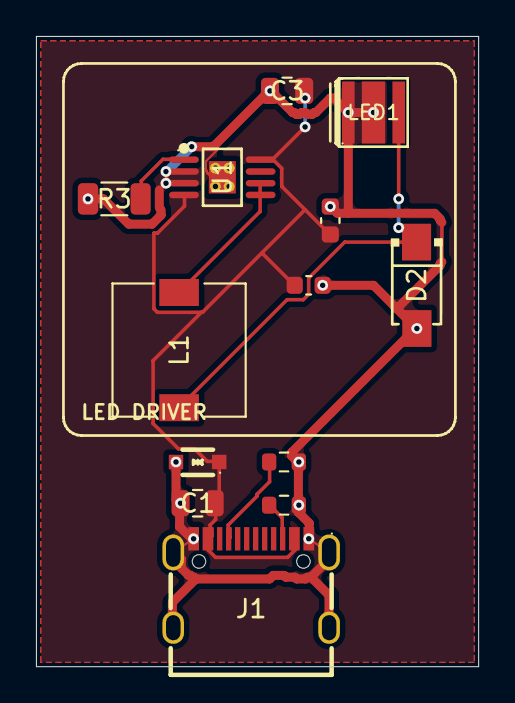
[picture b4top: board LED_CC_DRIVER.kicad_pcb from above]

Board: 2 copper layers, 24.6 x 35.0 mm, 13 parts (0 on the bottom side), 7 nets.

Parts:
C1, C3: 10uF; C_0805_2012Metric
C2: 100nF; C_0603_1608Metric
C4: 1uF; C_0603_1608Metric
D1: SD05C; SOD-323_L1.7-W1.3-LS2.5-BI
D2: SS14; SMA_L4.3-W2.6-LS5.0-RD
J1: USB-C Receptacle 16P; USB-C_SMD-TYPE-C-31-M-12_1
L1: 47uH; L_7.3x7.3_H3.5
LED1: JNJ-LTJW0115W120/63MIL; LED-SMD_3P-L3.5-W3.5-RD-C
R1, R2: 5.1k; R_0603_1608Metric
R3: 0.1; R_1206_3216Metric
U1: AL8860MP-13; MSOP-8_L3.0-W3.0-P0.65-LS4.9-BL-EP1.8

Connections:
CC1: J1.A5, R1.1
CC2: J1.B5, R2.1
GND: C1.2, C2.2, C3.2, C4.2, D1.2, D2.2, J1.1, J1.2, J1.3, J1.4, J1.A1B12, J1.B1A12, LED1.1, LED1.3, R1.2, R2.2, R3.2, U1.2, U1.3, U1.9
LED_ANODE: D2.1, L1.2, LED1.2
SET: R3.1, U1.1
SW: L1.1, U1.5, U1.6
VBUS: C1.1, C2.1, C3.1, C4.1, D1.1, J1.A4B9, J1.B4A9, U1.4, U1.8

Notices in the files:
README.md:
License:
MIT
